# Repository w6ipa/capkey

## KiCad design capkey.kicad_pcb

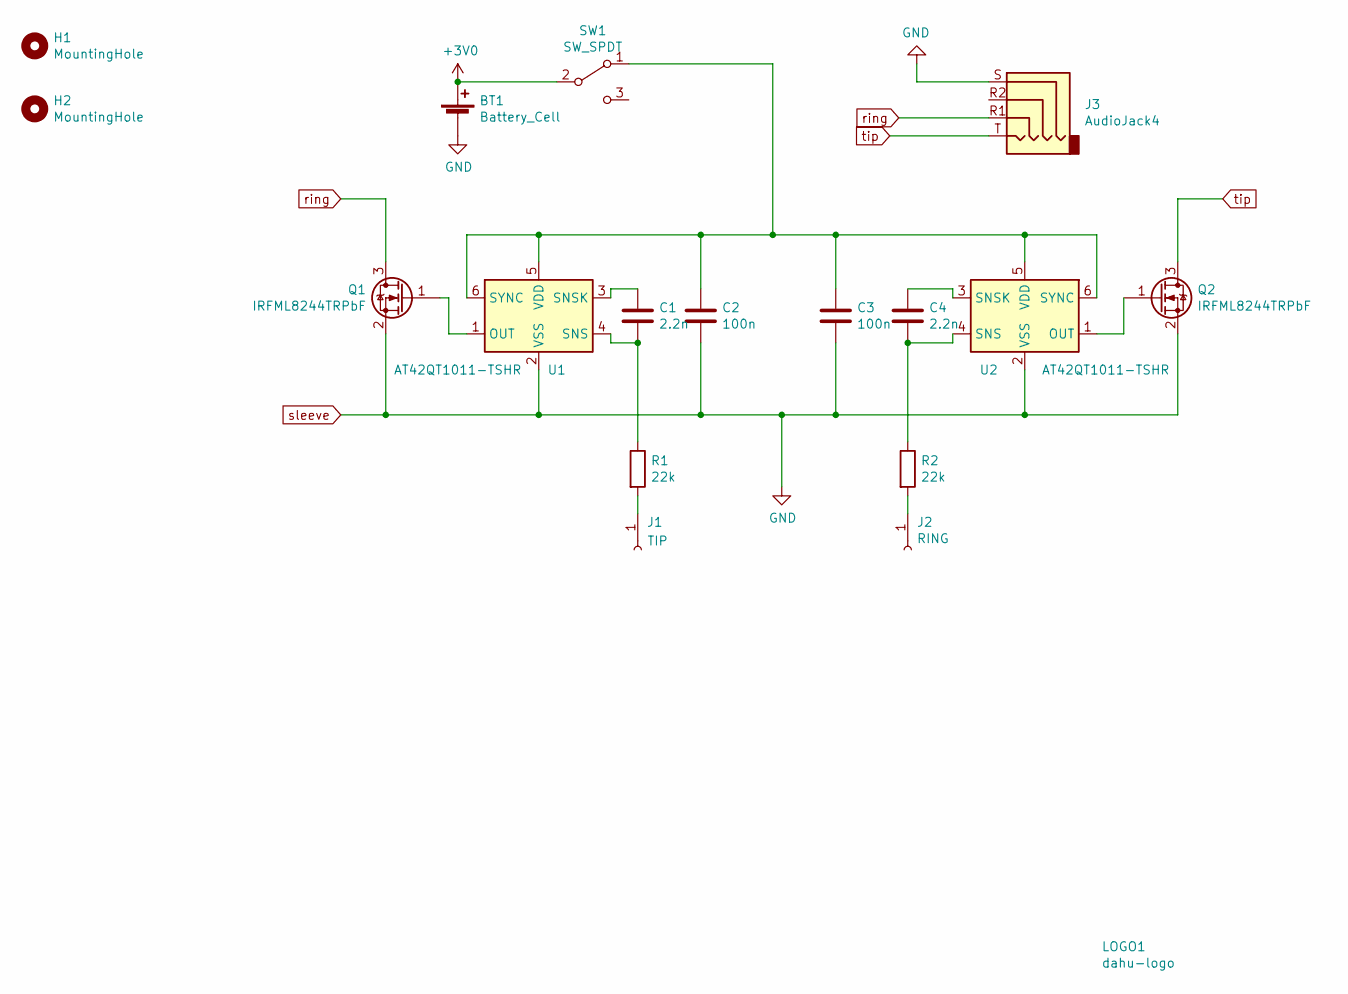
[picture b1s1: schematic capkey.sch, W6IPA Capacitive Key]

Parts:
BT1: Battery_Cell; BatteryHolder_Keystone_103_1x20mm
C1, C4: 2.2n; C_0805_2012Metric
C2, C3: 100n; C_0805_2012Metric
H1, H2: MountingHole; MountingHole_2.5mm
J1: TIP; SolderWirePad_1x01_Drill1.5mm
J2: RING; SolderWirePad_1x01_Drill1.5mm
J3: AudioJack4; KoreanHROparts_Jack-3.5mm-PJ3200B
LOGO1: dahu-logo; W6IPA-Logo-9mmx8mm
Q1, Q2: IRFML8244TRPbF; SOT-23
R1, R2: 22k; R_0805_2012Metric
SW1: SW_SPDT; SW_Slide_1P2T_CK_OS102011MS2Q
U1, U2: AT42QT1011-TSHR; SOT-23-6

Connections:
+3V0: BT1.1 (+), SW1.2 (B)
unnamed: C1.1, U1.3 (SNSK)
unnamed: C1.2, R1.1, U1.4 (SNS)
unnamed: C2.1, C3.1, SW1.1 (A), U1.5 (VDD), U1.6 (SYNC), U2.5 (VDD), U2.6 (SYNC)
unnamed: C4.1, U2.3 (SNSK)
unnamed: C4.2, R2.1, U2.4 (SNS)
unnamed: J1.1, R1.2
unnamed: J2.1, R2.2
unnamed: Q1.1 (G), U1.1 (OUT)
unnamed: Q2.1 (G), U2.1 (OUT)
ring: J3.R1, Q1.3 (D)
sleeve: BT1.2 (-), C2.2, C3.2, J3.S, Q1.2 (S), Q2.2 (S), U1.2 (VSS), U2.2 (VSS)
tip: J3.T, Q2.3 (D)

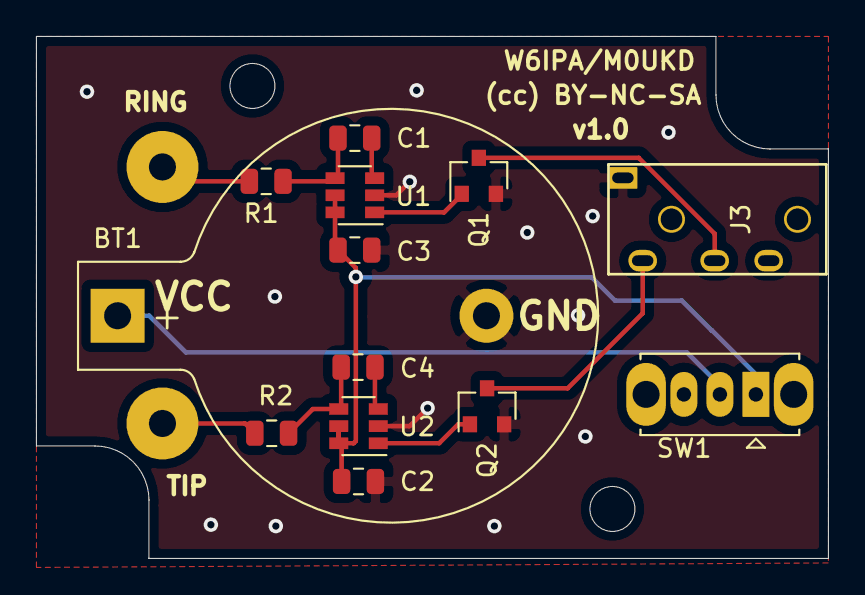
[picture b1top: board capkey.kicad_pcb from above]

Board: 2 copper layers, 44.0 x 29.0 mm, 18 parts (1 on the bottom side), 13 nets.

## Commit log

2020-02-05 Added attiny keyer
2020-02-06 7805 -> 7833
2020-02-07 switched paddle sides
2020-02-18 v1.0
